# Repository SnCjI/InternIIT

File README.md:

# Microscope Illumination Drivers — IIT Kharagpur Summer Internship 2026

Hi! This is where I keep everything I built during the **IEEE EMBS Summer Internship 2026** at IIT Kharagpur. The internship was virtual, organized by the IEEE EMBS Student Branch Chapter, the IEEE Student Branch and the IEEE Kharagpur Section.

My task was to design the electronics that illuminate the sample in a scanning microscope. I worked on it in two phases:

- [**Phase 1 — Multispectral LED driver**](phase1-led-driver/): a board that powers five high-power LEDs (UV, blue, green, red and near-infrared). An ESP32 dims each color with PWM, and a MEAN WELL LDD-H module keeps the current steady. This phase is finished: it's designed, simulated and ready to send to a PCB manufacturer.
- [**Phase 2 — DPSS laser driver**](phase2-dpss-laser-driver/): a board that drives four DPSS lasers, starting with a Thorlabs DJ532-40 (532 nm, green). A Raspberry Pi Pico 2 sets each laser's current and decides exactly when each one turns on, in step with the camera and the motorized stage. The design is complete in simulation, and a few details are waiting on my supervisor.

One thing to know up front: **I did all of this in simulation.** I didn't buy parts or build a board. The results come from circuit simulators (Proteus and ngspice), firmware simulators (Velxio, Wokwi, a PIO emulator and a board model I wrote in Python) and KiCad's design checks. Both boards are ready to be manufactured, but neither has been tested on a real bench yet.

<p align="center">
  
  <br><em>The Phase 2 setup: the PC runs the camera and the stage, and my board handles the lasers.</em>
</p>

---

## The idea behind both boards

When a microscope takes pictures at several wavelengths, the light source has two jobs. It has to switch colors quickly, and it has to give the same amount of light every single time. I approached both phases the same way.

First, I kept "how much current" separate from "when". A dedicated analog circuit regulates the current through the LED or laser, so the microcontroller never carries that current. It only decides when the light is on and what the target current should be.

Second, I let the hardware handle the timing. In Phase 1, the ESP32's LEDC peripheral generates the PWM by itself. In Phase 2, the Pico 2's PIO state machines switch the lasers and record the camera and stage signals with nanosecond resolution, without the CPU getting involved.

Third, I tried to catch problems before building anything. I simulated each block on its own and then together, and I kept fixing the PCBs until KiCad's electrical and design-rule checks came back clean.

---

## What I've done so far

### Phase 1: the LED driver (October 2026)

I started by writing the requirements for a five-channel driver and drew the schematic in KiCad, then laid out a two-layer 118 × 43 mm board. Both passed KiCad's checks with zero errors.

Before routing, I went through every connection against the datasheets. That review caught two mistakes that would have made the board useless: the transistor's pins were in the wrong order, and the LEDs were wired backwards. I also wrote the ESP32 firmware, which takes simple text commands over USB, and tested it in a simulator.

In Proteus and ngspice I checked three things: that the current stays steady, that the PWM switches cleanly, and that the LED's average current follows the duty cycle in a straight line. To finish the phase, I prepared everything a manufacturer needs (Gerbers, drill files, parts list and placement file) and wrote the report in IEEE format.

The step-by-step details are in [`phase1-led-driver/`](phase1-led-driver/).

### Phase 2: the laser driver (November 2026)

The requirements went through three revisions with my supervisor. To know what I was driving, I built an ngspice model of the DJ532-40 laser and fitted it to its datasheet.

Then I designed the current channel. It gives 160 mA per volt, has a hardware limit at 400 mA, and switches in 8.3 µs without overshooting. The full schematic uses 183 real parts across several sheets, and it goes on a four-layer 170 × 120 mm board that passes all of KiCad's checks.

Safety got its own circuit. The key switch, the interlock, a temperature signal and a watchdog all have to agree before the lasers can turn on. When I simulated it, I found that in the worst case it cut the laser off too slowly: 1.45 ms, against a 1 ms requirement. I fixed it in a second revision (Rev B), which brought it down to 0.18 ms.

The firmware is in MicroPython and uses the Pico's PIO for the timing. There's also a Python client for the PC. It passes 15 out of 15 unit tests, and I also ran it on a virtual Pico.

Finally, I simulated the whole system, including how the camera reads its sensor one line at a time. That simulation showed which camera setting has to be used; with the wrong one, most of the image comes out dark. I closed the phase with the Rev B fabrication files and an IEEE-format report.

The step-by-step details are in [`phase2-dpss-laser-driver/`](phase2-dpss-laser-driver/).

---

## What comes next

These are the next steps, roughly in the order I'd tackle them:

1. **Confirm the open details with my supervisor**: the voltage and direction of the stage's BNC signal, what form the temperature-OK signal takes, the camera settings (Status Expos and trigger mode), and the specs of the other three lasers.
2. **Use a bigger −3.3 V converter in Phase 2.** With all four lasers at 400 mA, the current converter runs at 77 % of its rating. A 5 A part such as the LM2678-ADJ would bring it under my 50 % target.
3. **Re-run the Phase 2 current-channel simulation** with the manufacturers' own models of the OPA4197 and NDT3055L.
4. **Make a Phase 1 board v1.1.** It needs pull-up resistors on the PWM inputs so the LEDs stay off while the ESP32 boots, and screw terminals in place of the LED footprints for the COB LEDs.
5. **Build the boards and measure them**: the LDD-H dimming, how fast the laser really responds, the safety-chain timing and the PC trigger delay. The Phase 2 board time-stamps most of this on its own.
6. **Calibrate each laser** and give each one its own current limit.
7. **Improve the firmware.** One rule is too cautious, and relaxing it would save about 57 ms at every stage position. I'd also add a check that confirms the camera setting before each scan starts.

---

## Repository map

```
.
├── README.md                     ← you are here
├── docs/images/                  figures used in the READMEs
├── phase1-led-driver/
│   ├── README.md                 step-by-step explanation of Phase 1
│   ├── report/                   IEEE-format report (PDF)
│   ├── kicad/                    KiCad 10 project (schematic + PCB)
│   ├── fabrication/              Gerbers, drill, BOM, positions, schematic PDF, ready-to-order ZIP
│   ├── firmware/                 ESP32 Arduino sketch
│   └── simulation/               Proteus projects, ngspice netlist, CSV results, plots
└── phase2-dpss-laser-driver/
    ├── README.md                 step-by-step explanation of Phase 2
    ├── docs/                     IEEE-format report + requirements & architecture (Rev 3)
    ├── kicad/                    KiCad 10 hierarchical project (5 sheets + PCB)
    ├── fabrication/              Gerbers (4 layers), drill, BOM, positions, PCB images, ZIP (Rev B)
    ├── firmware/                 MicroPython + PIO firmware, PC client, simulators and tests
    └── simulation/               ngspice and Python simulations, Steps 1, 2, 4 and 6
```

## Tools I used

KiCad 10 · Freerouting · Proteus 8 · ngspice · Python (NumPy, Matplotlib) · Arduino / ESP32 · MicroPython · Raspberry Pi Pico 2 PIO · Wokwi · Velxio

## About me

**Julia Isabel Sanchez Cruz**, a 4th-year Electronic Engineering student.
Summer Internship 2026 (virtual), IEEE EMBS SBC, IEEE SB and IEEE Kharagpur Section, IIT Kharagpur.

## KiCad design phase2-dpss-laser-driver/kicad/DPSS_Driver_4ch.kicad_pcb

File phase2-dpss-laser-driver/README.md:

# Phase 2 — Four-Channel DPSS Laser Driver with Camera and Stage Synchronization

**Raspberry Pi Pico 2 (MicroPython + PIO) · DAC8565 · OPA4197 / NDT3055L current sinks · hardware safety chain · KiCad 10 · ngspice / Python**

Phase 2 replaces the LEDs of Phase 1 with **DPSS lasers** (diode-pumped solid-state), starting with the **Thorlabs DJ532-40** (532 nm, 40 mW), and adds what a scanning microscope needs: every image must be taken **with exactly one laser on, at a known time, after the stage has stopped moving**.

The system has three players:

- **Host PC (the master):** holds the scan plan, moves the Holmarc XYZ-θ stage, controls the PCO.panda 4.2 bi camera and stores the images.
- **Driver board (this project):** a Pico 2 that sets the four laser currents and switches each laser on and off in sync with the stage and camera signals.
- **Hardware safety chain:** key switch, interlock, temperature-OK and a watchdog that cut the laser current **without depending on the firmware**.

As in Phase 1, everything was verified in simulation; no hardware was built.

Report (IEEE format): [`docs/DPSS_Laser_Driver_Phase2_Report_IEEE.pdf`](docs/DPSS_Laser_Driver_Phase2_Report_IEEE.pdf)
Requirements and architecture, Rev 3: [`docs/DPSS_Laser_Driver_Phase2_Requirements_Architecture_Rev3.pdf`](docs/DPSS_Laser_Driver_Phase2_Requirements_Architecture_Rev3.pdf)

---

## How one stage position works

For every position of the snake-by-row scan, the board runs this sequence once per laser. The Pico's PIO state machines execute it in hardware, so the CPU doesn't have to:

```
stage "in position" edge → wait SETTLE → laser k ON → wait LEAD (laser output stabilizes)
→ camera exposure → camera's Status Expos falls → laser k OFF (13 ns later) → wait GAP → next laser
```

Each image therefore gets light from only one laser. Two more state machines time-stamp every stage and camera edge with nanosecond resolution and send the time stamps to the PC.

---

## Step by step: what was done

### Step 0 — Requirements and architecture (3 revisions)

The supervisor set the main decisions: four lasers switched only through their drive current, the PC as master, Python as the language, microsecond-level trigger timing, and the camera treated as something that must never be put at risk. From these I wrote 23 requirements, grouped as functional (F), electrical (E), safety (S), interface (I) and thermal (T), each with a test. The document went through **three revisions**. Revision 3 corrected a camera setting that the simulation in Step 6 showed was wrong.

### Step 1 — A model of the laser

The DJ532-40 was modeled in **ngspice**: a pump diode fitted to the datasheet's voltage curve, plus a green output that grows with the square of the current above threshold (the laser uses frequency doubling), P = K(I − I<sub>th</sub>)², with K = 1.027 W/A² and I<sub>th</sub> = 162 mA.

The datasheet does not give the optical response time τ, so I swept it from 10 µs to 1 ms. With a **5 ms lead time** before each exposure, the light deficit is below 0.07 % even in the worst case.

### Step 2 — One current channel

Each channel is a **linear current sink**: no switching ripple and a predictable step response. That matters because the DJ532-40 has only 70 mA between its typical (330 mA) and maximum (400 mA) current. The laser's case is its anode, so the anode stays at ground and the current is pulled from the cathode into a −3.3 V rail.

The DAC voltage passes an analog switch only when ENABLE **and** LASER_ON are high. It is then clamped to 2.5 V, level-shifted and fed to the control amplifier, which drives an NDT3055L MOSFET over a 1 Ω sense resistor. The result is **I = 160 mA/V × V<sub>DAC</sub>**, with a hardware ceiling of **400 mA** at the 2.5 V clamp.

| Test | Result |
|---|---|
| DC transfer | 160.00 mA/V, offset 0.08 mA |
| Hardware clamp (DAC up to 3.3 V) | 400.1 mA |
| Switching | 10–90 % in 8.3 µs, **0 % overshoot** |
| Power-up with the DAC at 3.3 V | 0.000 mA |
| Reverse voltage kick | 0.47 V (laser limit 2 V) |
| Compliance at −5 % rail | 400 mA with V<sub>DS</sub> = 0.54 V |

### Step 3 — Full schematic with real parts

A hierarchical KiCad project: a top sheet, power, controller (Pico 2, DAC, camera, stage and temperature interfaces), safety, and one laser-channel sheet used four times. In total **183 parts and 144 nets**.

| Function | Part |
|---|---|
| Controller | Raspberry Pi Pico 2 (RP2350) |
| Set-point DAC | DAC8565, 16 bit, 4 channels, 2.5 V reference |
| Op-amps | OPA4197 (quad) |
| Current sink | NDT3055L (SOT-223) |
| Safety logic | 74LVC2G17 Schmitt buffer, 74LVC1G11 AND, 74LVC2G74 latch, TPS3823 watchdog |
| Laser short when disabled | G6K-2F-Y relay |
| Power | LM2596S-5.0, LM2596S-ADJ (inverting, −3.31 V), TPS60403 (−5 V) |

### Step 4 — Safety chain simulation (and the Rev B fix)

The key switch and interlock close a CHAIN line. CHAIN, TEMP_OK and the watchdog go into an AND gate that clears a latch. The latch output is **ENABLE**, which gates all four channels, releases the shorting relays and lights the emission LED. ENABLE comes back only when everything is OK **and** the firmware sends a reset edge.

I simulated the whole path, from the interlock contact to the laser light. **This found a real problem.** With the original 10 kΩ/100 nF filter, CHAIN falls slowly into a normal CMOS input. With typical thresholds the laser turned off in 0.82 ms, but with the worst-case input threshold it took **1.45 ms**, which fails the 1 ms requirement.

**Rev B** added a Schmitt buffer (74LVC2G17) and reduced the capacitor to 10 nF. Worst case is now **0.18 ms**.

| Case | Current below 1 % | Requirement S1 (≤ 1 ms) |
|---|---|---|
| Interlock, Rev A, typical | 0.82 ms | Pass |
| Interlock, Rev A, worst case | 1.45 ms | **Fail** |
| Interlock or key, Rev B | 0.18 ms | Pass |
| TEMP_OK lost, Rev B | 0.075 ms | Pass |
| Watchdog reset | 0.032 ms | Pass |

### Step 5 — Firmware (MicroPython + PIO)

The firmware is six MicroPython files, and only one of them (`hw_pico.py`) touches the hardware. That lets the same core run on the Pico and in the PC simulators. Three PIO programs handle the timing: `frame_seq` runs the frames, `edge_ts` time-stamps edges, and `pulse` drives the stage output.

Safety in firmware: at power-up everything is zero and disabled. Set points above the per-laser limit (default 330 mA) are rejected. Any fault switches the lasers off, zeroes the DAC and **stops feeding the watchdog**, so the hardware latch opens too.

With no hardware available, the firmware was validated four ways:

| Check | Result |
|---|---|
| PIO opcodes vs. an independent assembler | 36/36 identical |
| MicroPython syntax (mpy-cross) | 6/6 files compile |
| Unit tests against the requirements | **15/15 pass** |
| Interval error (100 random intervals, cycle-accurate) | ≤ 3.3 ns (requirement 1 µs) |
| Time-stamp error (120 edges) | ≤ 6.7 ns |
| End of exposure → laser off | 13.3 ns |
| Snake scan 4 × 5 positions × 4 lasers | 80/80 images correctly lit |
| Real firmware on a virtual Pico (Wokwi) | Boot, fault, hardware-timed frame: OK |

Two bugs were found and fixed this way: the stage and camera pins were not configured as inputs, and the main loop did not yield to the USB stack.

See [`firmware/README.md`](firmware/README.md) for the full command set and how to run the verification (`python run_all.py`).

### Step 6 — Camera and stage synchronization

The PC client ran complete snake scans against the simulated board, with a **rolling-shutter camera model** built from the pco.panda manual. The camera's 2048 lines start one after another, 12.17 µs apart, so the last line starts 24.9 ms after the first.

**Finding 1: the camera setting matters.** The board turns the laser off when the camera's Status Expos signal falls, so that signal has to cover the exposure of *every* line. Only the setting **"Status Expos = overall time of All lines"** lights every row. With "First Line", 1555 of the 2048 rows got less than half the light, and that is the kind of mistake no electrical check would ever catch. Revision 2 of the requirements had specified a different setting; Revision 3 fixes it.

**Finding 2: who triggers the camera.** I compared mode B (the board triggers the camera) with mode A (the PC triggers it by software), using three assumed PC latency profiles. Each case ran 400 images:

| Mode | Exposure start after laser stable | Unused light per image | 4 × 5 scan time |
|---|---|---|---|
| B (board) | 0.031 ms | 5.0 ms | 10.44 s |
| A1 (tuned PC loop) | 1.5 ms | 6.5 ms | 10.57 s |
| A2 (typical Python) | 3.4 ms | 8.4 ms | 10.71 s |
| A3 (15.6 ms Windows timer) | 9.9 ms | 14.9 ms | 11.23 s |

Every image came out correct in every mode: a late trigger costs time, not images. **Mode A is recommended** because it needs no electrical connection to the camera input, and it only costs 1–8 % of scan time. Mode B is still on the board for when repeatable microsecond timing is needed.

### Step 7 — PCB and fabrication package (Rev B)

- **Four layers, 170 × 120 mm.** Power at the top left, Pico 2 in the center, camera, stage and safety at the top right, and the four channels along the bottom, each next to its laser connector.
- **Layer stack:** In1 is a solid ground plane. In2 carries the −3.3 V laser rail under the channels and ground elsewhere. Each MOSFET drain has its own copper area for heat.
- **Routing:** done with Freerouting using net classes (1 mm for laser currents, 0.3 mm for power, 0.25 mm for signals).
- **Checks:** KiCad 10 **ERC 0 errors**; **DRC 0 errors, 0 unconnected, 0 parity differences**. The checks were repeated after Rev B.

### Thermal check and test report

The laser channels are well within margin (the MOSFET runs at 35 % of its rating). **The weak point is the −3.3 V inverting converter.** With all four lasers at 400 mA its switch reaches 2.3 A peak, which is 77 % of its 3 A rating. That's above the 50 % target, although at the default 330 mA limit it drops to 65 %.

The test report has 19 test cases: **17 pass**. TC-07 is the failure that led to Rev B (fixed and re-tested as TC-08), and TC-19 (thermal and stress margin) passes only partly because of the converter.

---

## Future objectives for Phase 2

**Waiting on the supervisor**
- [ ] Confirm the stage's BNC signal: voltage level, direction and real step time (300 ms was assumed)
- [ ] Confirm the electrical form of the temperature-OK signal
- [ ] Confirm the camera settings: Status Expos = "overall time of All lines", and trigger mode A
- [ ] Get the specifications of the other three DPSS lasers

**Design improvements**
- [ ] Upsize the −3.3 V converter to a 5 A part (for example LM2678-ADJ with a 5 A Schottky), or use one converter per two channels
- [ ] Repeat the Step 2 simulation with the vendor SPICE models of the OPA4197 and NDT3055L
- [ ] Relax the firmware GAP rule (GAP + LEAD ≥ 25 ms is conservative), saving about 57 ms per stage position
- [ ] Before every scan, have the PC compare the measured Status Expos width with the expected value (exposure + 24.9 ms) to catch a wrong camera setting

**Hardware**
- [ ] Fabricate and assemble the board
- [ ] Measure the real DPSS response time τ (a short τ allows a shorter LEAD), the safety-chain timing, and the PC trigger latency using the board's own time stamps
- [ ] Calibrate the current limit of each laser module

---

## Folder contents

| Path | What is inside |
|---|---|
| `docs/` | Phase 2 report (IEEE, 8 pages) and Requirements & Architecture Rev 3 (7 pages) |
| `kicad/` | KiCad 10 hierarchical project: `DPSS_Driver_4ch.kicad_sch` (top), `power`, `controller`, `safety`, `laser_channel` sheets, `.kicad_pcb`, `.kicad_pro` |
| `fabrication/gerbers/` | 4 copper, 2 mask, 2 paste, 2 silkscreen, outline, job file, PTH/NPTH drill + drill maps |
| `fabrication/assembly/` | Grouped BOM and pick-and-place file |
| `fabrication/docs/` | Schematic PDF, top/bottom PCB images, Gerber preview |
| `fabrication/DPSS_Driver_4ch_Fabrication_Package_RevB.zip` | Everything above in one file, ready to send to a PCB maker |
| `firmware/firmware/` | The six MicroPython files that go on the Pico 2 |
| `firmware/pc/` | PC client (pyserial) and a snake-scan example |
| `firmware/sim/` | PIO assembler check, PIO emulator runs, board model, unit tests, Step 6 camera models; results in `sim/results/` |
| `firmware/wokwi/` | Files to run the firmware on a virtual Pico in Wokwi |
| `simulation/Step1_DPSS_model/` | ngspice laser model and fit |
| `simulation/Step2_Current_channel/` | ngspice channel tests (DC, gate, power-up, reverse, compliance) |
| `simulation/Step4_Safety_chain/` | ngspice/XSPICE safety-chain cases A–E, results CSV |
| `simulation/Step6_Camera_modes/` | Rolling-shutter results, mode A vs B, Status Expos settings |

Each simulation folder has its own `README.txt` with the exact commands to re-run it.

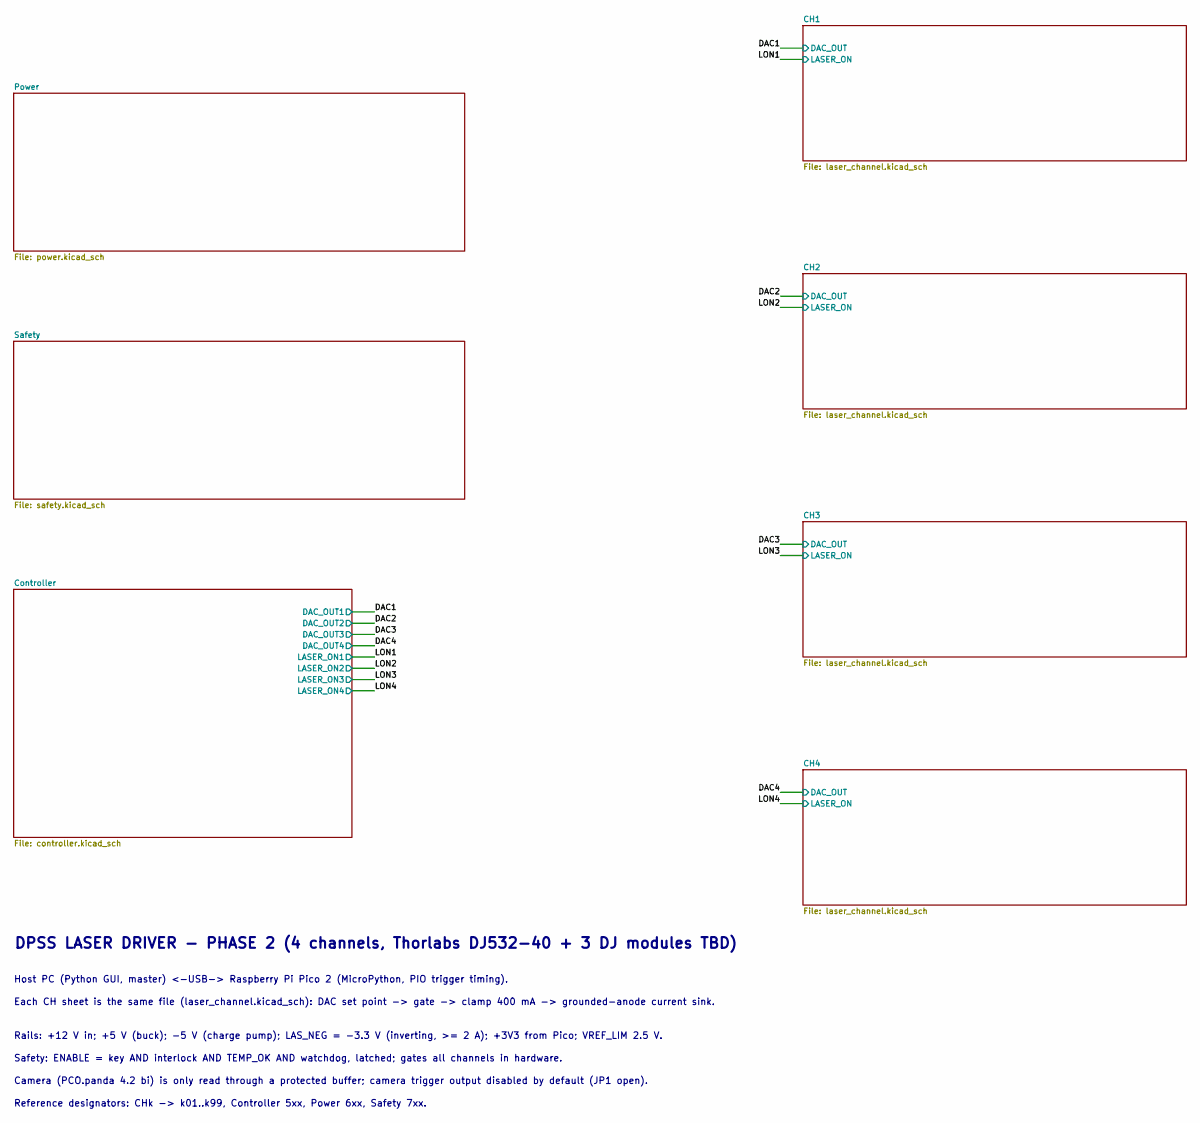
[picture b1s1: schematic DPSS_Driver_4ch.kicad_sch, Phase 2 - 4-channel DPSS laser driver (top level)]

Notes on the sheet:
Reference designators: CHk -> k01..k99, Controller 5xx, Power 6xx, Safety 7xx.
Camera (PCO.panda 4.2 bi) is only read through a protected buffer; camera trigger output disabled by default (JP1 open).
Host PC (Python GUI, master) <-USB-> Raspberry Pi Pico 2 (MicroPython, PIO trigger timing).
DPSS LASER DRIVER - PHASE 2 (4 channels, Thorlabs DJ532-40 + 3 DJ modules TBD)
Safety: ENABLE = key AND interlock AND TEMP_OK AND watchdog, latched; gates all channels in hardware.
Rails: +12 V in; +5 V (buck); -5 V (charge pump); LAS_NEG = -3.3 V (inverting, >= 2 A); +3V3 from Pico; VREF_LIM 2.5 V.
Each CH sheet is the same file (laser_channel.kicad_sch): DAC set point -> gate -> clamp 400 mA -> grounded-anode current sink.

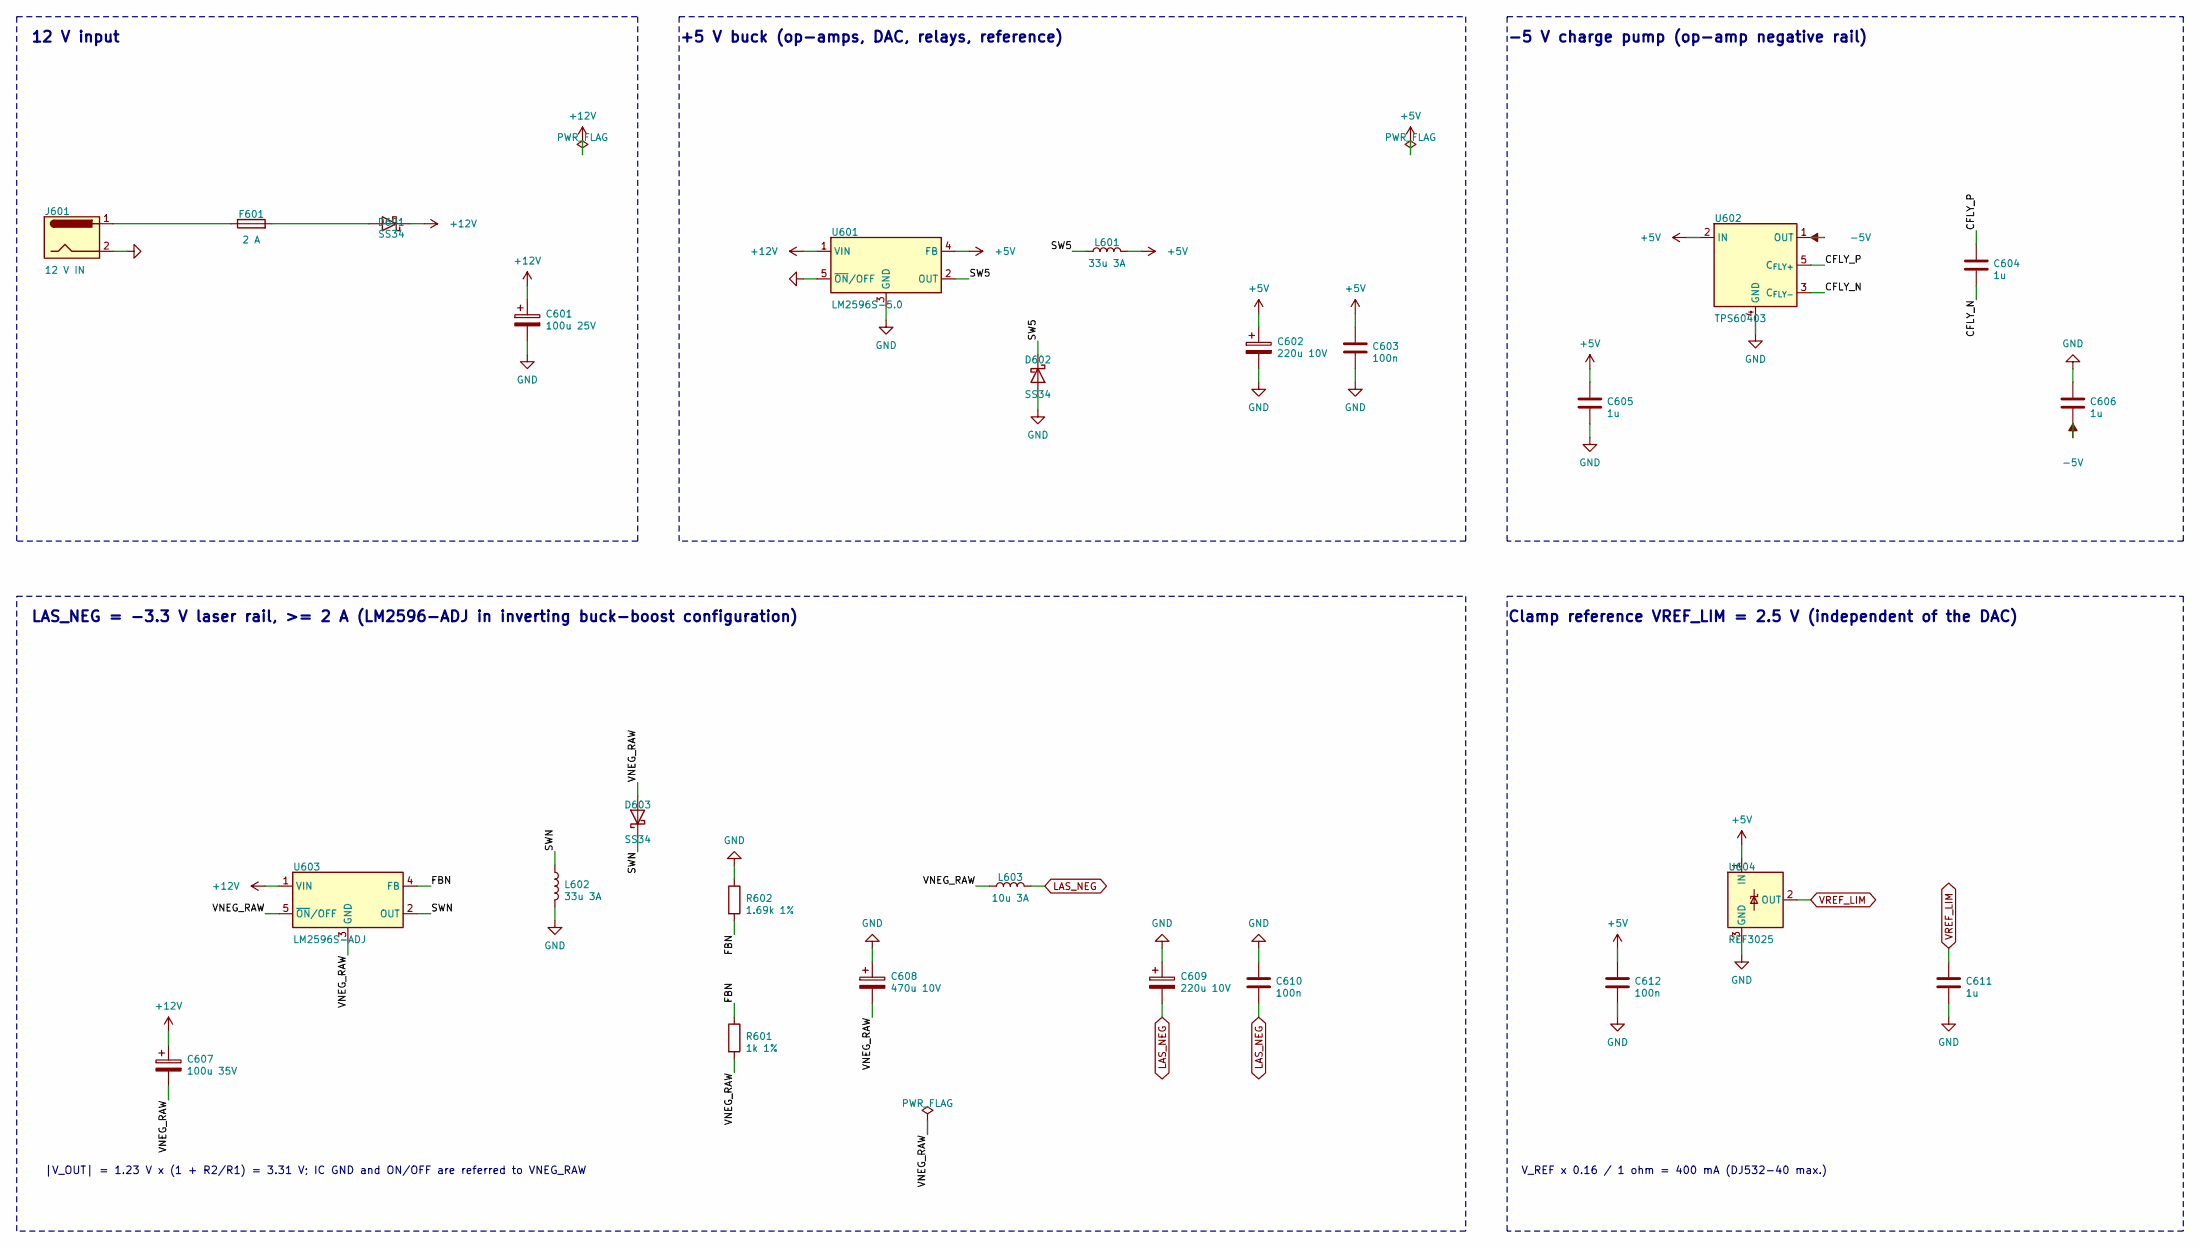
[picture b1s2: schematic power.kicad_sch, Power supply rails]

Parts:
C601: 100u 25V; CP_Elec_8x10
C602, C609: 220u 10V; CP_Elec_8x10
C603, C610, C612: 100n; C_0805_2012Metric
C604, C605, C606, C611: 1u; C_0805_2012Metric
C607: 100u 35V; CP_Elec_8x10
C608: 470u 10V; CP_Elec_10x10
D601, D602, D603: SS34; D_SMA
F601: 2 A; Fuse_1812_4532Metric
J601: 12 V IN; BarrelJack_Horizontal
L601, L602: 33u 3A; L_12x12mm_H8mm
L603: 10u 3A; L_6.3x6.3_H3
R601: 1k 1%; R_0805_2012Metric
R602: 1.69k 1%; R_0805_2012Metric
U601: LM2596S-5.0; TO-263-5_TabPin3
U602: TPS60403; SOT-23-5
U603: LM2596S-ADJ; TO-263-5_TabPin3
U604: REF3025; SOT-23

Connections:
+5V: C602.1, C603.1, C605.1, C612.1, L601.2, U601.4 (FB), U602.2 (IN), U604.1 (IN); also elsewhere on the board
+12V: C601.1, C607.1, D601.1 (K), U601.1 (VIN), U603.1 (VIN)
-5V: C606.2, U602.1 (OUT); also elsewhere on the board
/Power/CFLY_N: C604.2, U602.3 (C_{FLY-})
/Power/CFLY_P: C604.1, U602.5 (C_{FLY+})
/Power/FBN: R601.1, R602.2, U603.4 (FB)
/Power/SW5: D602.1 (K), L601.1, U601.2 (OUT)
/Power/SWN: D603.1 (K), L602.1, U603.2 (OUT)
/Power/VNEG_RAW: C607.2, C608.2, D603.2 (A), L603.1, R601.2, U603.3 (GND), U603.5 (~ON/OFF)
GND: C601.2, C602.2, C603.2, C605.2, C606.1, C608.1, C609.1, C610.1, C611.2, C612.2, D602.2 (A), J601.2, L602.2, R602.1, U601.3 (GND), U601.5 (~ON/OFF), U602.4 (GND), U604.3 (GND); also elsewhere on the board
LAS_NEG: C609.2, C610.2, L603.2; also elsewhere on the board
unnamed: D601.2 (A), F601.2
unnamed: F601.1, J601.1
VREF_LIM: C611.1, U604.2 (OUT); also elsewhere on the board

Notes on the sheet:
Clamp reference VREF_LIM = 2.5 V (independent of the DAC)
|V_OUT| = 1.23 V x (1 + R2/R1) = 3.31 V; IC GND and ON/OFF are referred to VNEG_RAW
+5 V buck (op-amps, DAC, relays, reference)
12 V input
-5 V charge pump (op-amp negative rail)
V_REF x 0.16 / 1 ohm = 400 mA (DJ532-40 max.)
LAS_NEG = -3.3 V laser rail, >= 2 A (LM2596-ADJ in inverting buck-boost configuration)

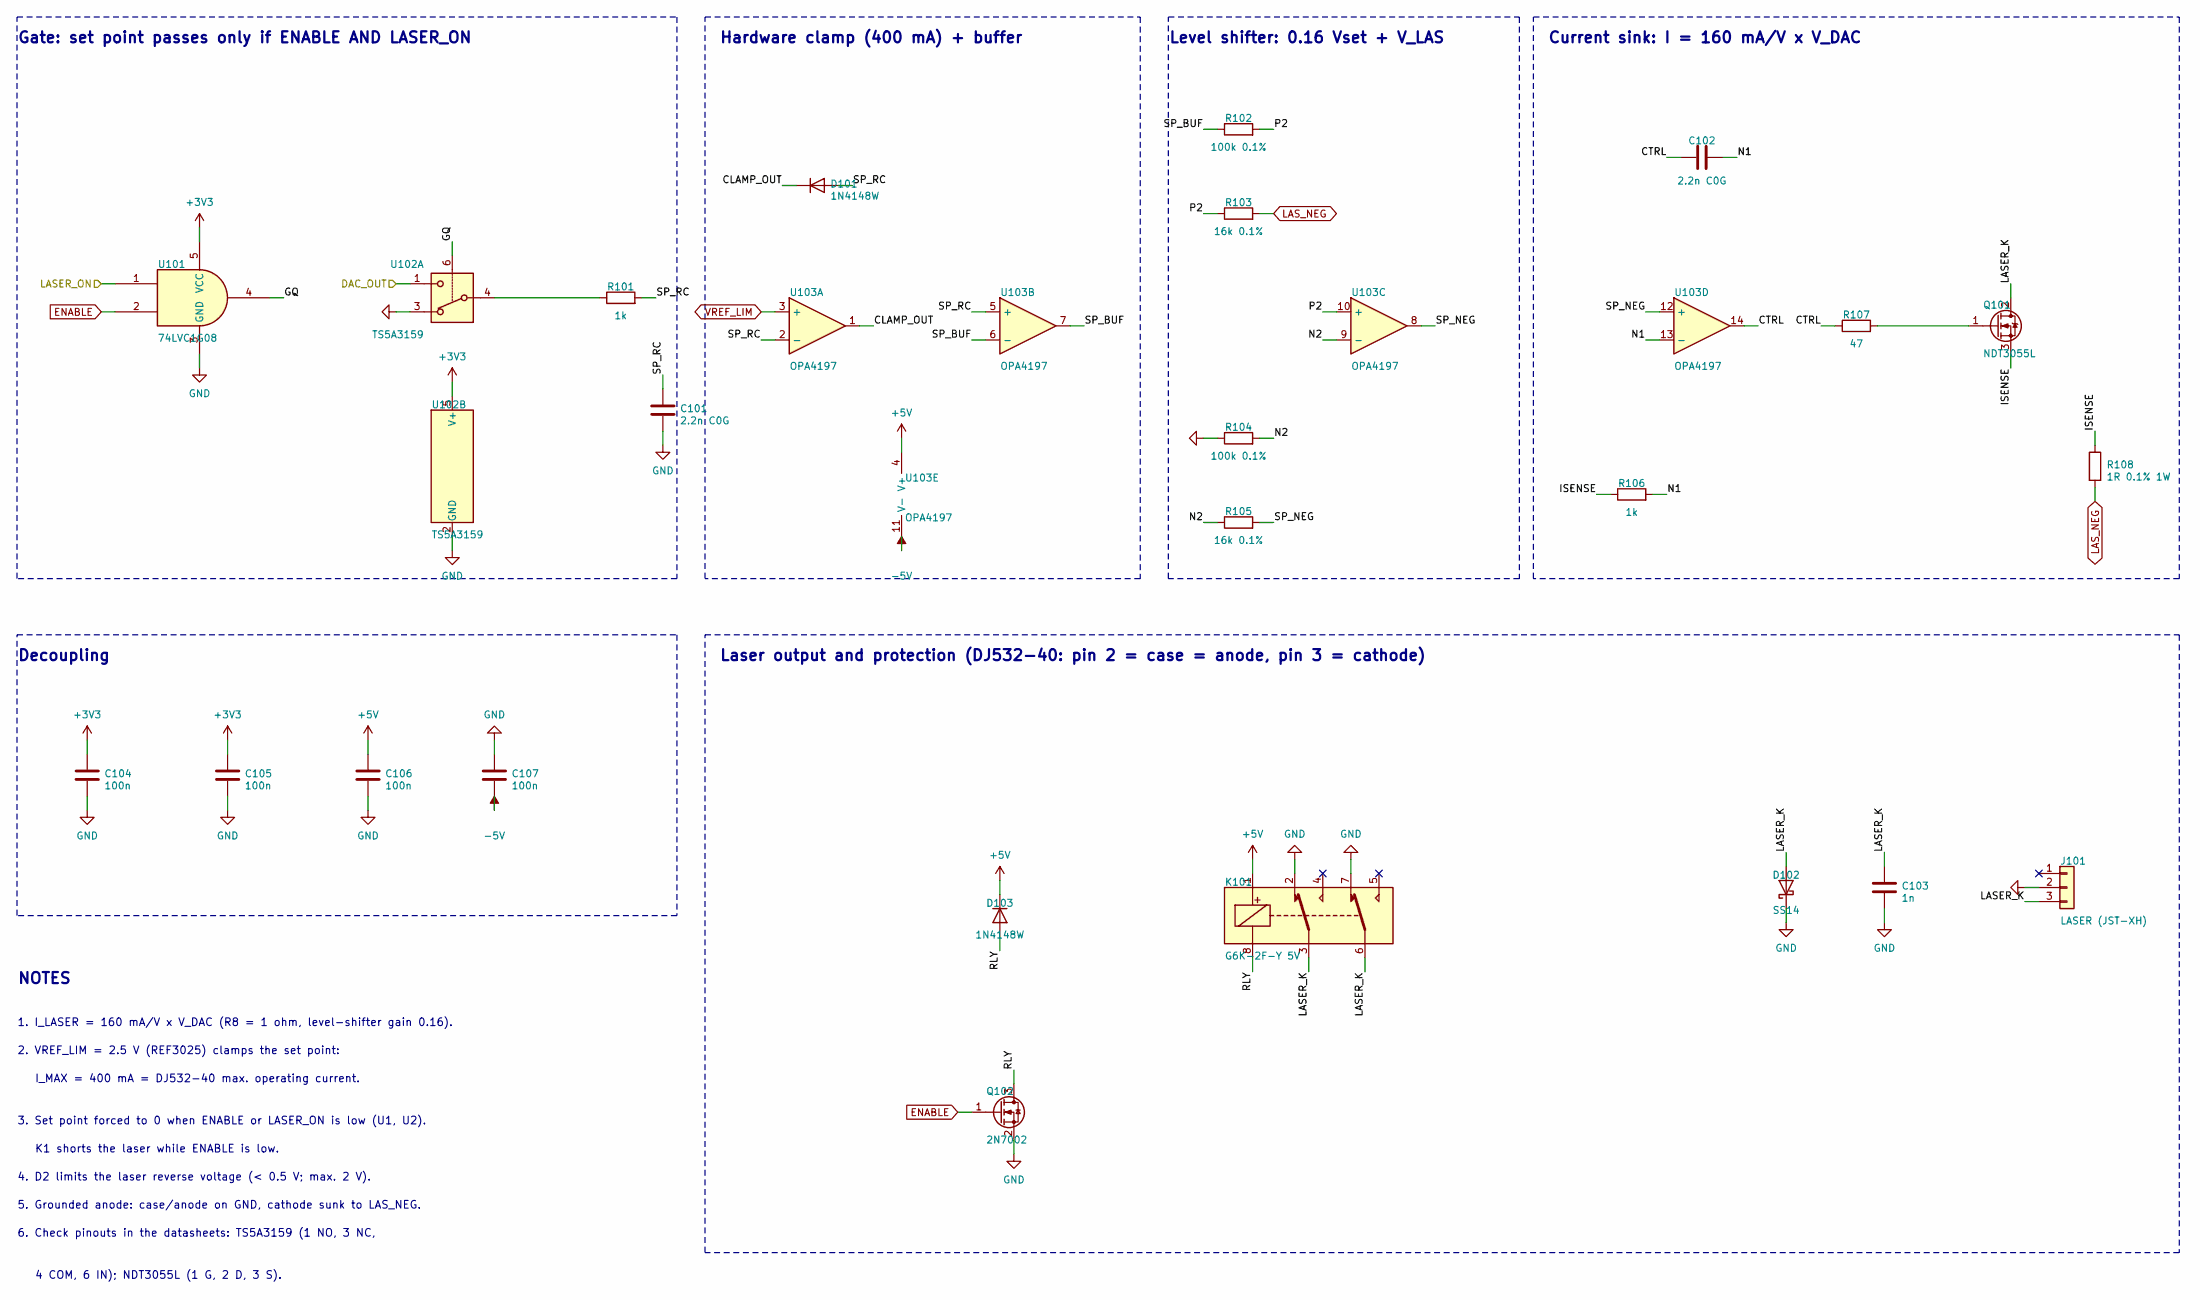
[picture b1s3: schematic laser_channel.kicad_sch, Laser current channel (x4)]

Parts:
C101, C102: 2.2n C0G; C_0805_2012Metric
C103: 1n; C_0805_2012Metric
C104, C105, C106, C107: 100n; C_0805_2012Metric
D101, D103: 1N4148W; D_SOD-123
D102: SS14; D_SMA
J101: LASER (JST-XH); JST_XH_B3B-XH-A_1x03_P2.50mm_Vertical
K101: G6K-2F-Y 5V; Relay_DPDT_Omron_G6K-2F-Y
Q101: NDT3055L; SOT-223-3_TabPin2
Q102: 2N7002; SOT-23
R101, R106: 1k; R_0805_2012Metric
R102, R104: 100k 0.1%; R_0805_2012Metric; Tolerance 0.1%
R103, R105: 16k 0.1%; R_0805_2012Metric; Tolerance 0.1%
R107: 47; R_0805_2012Metric
R108: 1R 0.1% 1W; R_2512_6332Metric; Tolerance 0.1%
U101: 74LVC1G08; SOT-23-5
U102: TS5A3159; SOT-23-6
U103: OPA4197; SOIC-14_3.9x8.7mm_P1.27mm

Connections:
+3V3: C104.1, C105.1, U101.5 (VCC), U102.5 (V+); also elsewhere on the board
+5V: C106.1, D103.1 (K), K101.1, U103.4 (V+); also elsewhere on the board
-5V: C107.2, U103.11 (V-); also elsewhere on the board
/CH1/CLAMP_OUT: D101.1 (K), U103.1
/CH1/CTRL: C102.1, R107.1, U103.14
/CH1/GQ: U101.4, U102.6
/CH1/ISENSE: Q101.3 (S), R106.1, R108.1
/CH1/LASER_K: C103.1, D102.2 (A), J101.3, K101.3, K101.6, Q101.2 (D)
/CH1/N1: C102.2, R106.2, U103.13 (-)
/CH1/N2: R104.2, R105.1, U103.9 (-)
/CH1/P2: R102.2, R103.1, U103.10 (+)
/CH1/RLY: D103.2 (A), K101.8, Q102.3 (D)
/CH1/SP_BUF: R102.1, U103.6 (-), U103.7
/CH1/SP_NEG: R105.2, U103.8, U103.12 (+)
/CH1/SP_RC: C101.1, D101.2 (A), R101.2, U103.2 (-), U103.5 (+)
/DAC1: U102.1; also elsewhere on the board
/LON1: U101.1; also elsewhere on the board
ENABLE: Q102.1 (G), U101.2; also elsewhere on the board
GND: C101.2, C103.2, C104.2, C105.2, C106.2, C107.1, D102.1 (K), J101.2, K101.2, K101.7, Q102.2 (S), R104.1, U101.3 (GND), U102.2 (GND), U102.3; also elsewhere on the board
LAS_NEG: R103.2, R108.2; also elsewhere on the board
unnamed: Q101.1 (G), R107.2
unnamed: R101.1, U102.4
VREF_LIM: U103.3 (+); also elsewhere on the board

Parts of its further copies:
C201, C202, C301, C302, C401, C402: 2.2n C0G; C_0805_2012Metric
C203, C303, C403: 1n; C_0805_2012Metric
C204, C205, C206, C207, C304, C305, C306, C307, C404, C405, C406, C407: 100n; C_0805_2012Metric
D201, D203, D301, D303, D401, D403: 1N4148W; D_SOD-123
D202, D302, D402: SS14; D_SMA
J201, J301, J401: LASER (JST-XH); JST_XH_B3B-XH-A_1x03_P2.50mm_Vertical
K201, K301, K401: G6K-2F-Y 5V; Relay_DPDT_Omron_G6K-2F-Y
Q201, Q301, Q401: NDT3055L; SOT-223-3_TabPin2
Q202, Q302, Q402: 2N7002; SOT-23
R201, R206, R301, R306, R401, R406: 1k; R_0805_2012Metric
R202, R204, R302, R304, R402, R404: 100k 0.1%; R_0805_2012Metric; Tolerance 0.1%
R203, R205, R303, R305, R403, R405: 16k 0.1%; R_0805_2012Metric; Tolerance 0.1%
R207, R307, R407: 47; R_0805_2012Metric
R208, R308, R408: 1R 0.1% 1W; R_2512_6332Metric; Tolerance 0.1%
U201, U301, U401: 74LVC1G08; SOT-23-5
U202, U302, U402: TS5A3159; SOT-23-6
U203, U303, U403: OPA4197; SOIC-14_3.9x8.7mm_P1.27mm

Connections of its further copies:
+3V3: C204.1, C205.1, C304.1, C305.1, C404.1, C405.1, U201.5 (VCC), U202.5 (V+), U301.5 (VCC), U302.5 (V+), U401.5 (VCC), U402.5 (V+); also elsewhere on the board
+5V: C206.1, C306.1, C406.1, D203.1 (K), D303.1 (K), D403.1 (K), K201.1, K301.1, K401.1, U203.4 (V+), U303.4 (V+), U403.4 (V+); also elsewhere on the board
-5V: C207.2, C307.2, C407.2, U203.11 (V-), U303.11 (V-), U403.11 (V-); also elsewhere on the board
/CH2/CLAMP_OUT: D201.1 (K), U203.1
/CH2/CTRL: C202.1, R207.1, U203.14
/CH2/GQ: U201.4, U202.6
/CH2/ISENSE: Q201.3 (S), R206.1, R208.1
/CH2/LASER_K: C203.1, D202.2 (A), J201.3, K201.3, K201.6, Q201.2 (D)
/CH2/N1: C202.2, R206.2, U203.13 (-)
/CH2/N2: R204.2, R205.1, U203.9 (-)
/CH2/P2: R202.2, R203.1, U203.10 (+)
/CH2/RLY: D203.2 (A), K201.8, Q202.3 (D)
/CH2/SP_BUF: R202.1, U203.6 (-), U203.7
/CH2/SP_NEG: R205.2, U203.8, U203.12 (+)
/CH2/SP_RC: C201.1, D201.2 (A), R201.2, U203.2 (-), U203.5 (+)
/CH3/CLAMP_OUT: D301.1 (K), U303.1
/CH3/CTRL: C302.1, R307.1, U303.14
/CH3/GQ: U301.4, U302.6
/CH3/ISENSE: Q301.3 (S), R306.1, R308.1
/CH3/LASER_K: C303.1, D302.2 (A), J301.3, K301.3, K301.6, Q301.2 (D)
/CH3/N1: C302.2, R306.2, U303.13 (-)
/CH3/N2: R304.2, R305.1, U303.9 (-)
/CH3/P2: R302.2, R303.1, U303.10 (+)
/CH3/RLY: D303.2 (A), K301.8, Q302.3 (D)
/CH3/SP_BUF: R302.1, U303.6 (-), U303.7
/CH3/SP_NEG: R305.2, U303.8, U303.12 (+)
/CH3/SP_RC: C301.1, D301.2 (A), R301.2, U303.2 (-), U303.5 (+)
/CH4/CLAMP_OUT: D401.1 (K), U403.1
/CH4/CTRL: C402.1, R407.1, U403.14
/CH4/GQ: U401.4, U402.6
/CH4/ISENSE: Q401.3 (S), R406.1, R408.1
/CH4/LASER_K: C403.1, D402.2 (A), J401.3, K401.3, K401.6, Q401.2 (D)
/CH4/N1: C402.2, R406.2, U403.13 (-)
/CH4/N2: R404.2, R405.1, U403.9 (-)
/CH4/P2: R402.2, R403.1, U403.10 (+)
/CH4/RLY: D403.2 (A), K401.8, Q402.3 (D)
/CH4/SP_BUF: R402.1, U403.6 (-), U403.7
/CH4/SP_NEG: R405.2, U403.8, U403.12 (+)
/CH4/SP_RC: C401.1, D401.2 (A), R401.2, U403.2 (-), U403.5 (+)
/DAC2: U202.1; also elsewhere on the board
/DAC3: U302.1; also elsewhere on the board
/DAC4: U402.1; also elsewhere on the board
/LON2: U201.1; also elsewhere on the board
/LON3: U301.1; also elsewhere on the board
/LON4: U401.1; also elsewhere on the board
ENABLE: Q202.1 (G), Q302.1 (G), Q402.1 (G), U201.2, U301.2, U401.2; also elsewhere on the board
GND: C201.2, C203.2, C204.2, C205.2, C206.2, C207.1, C301.2, C303.2, C304.2, C305.2, C306.2, C307.1, C401.2, C403.2, C404.2, C405.2, C406.2, C407.1, D202.1 (K), D302.1 (K), D402.1 (K), J201.2, J301.2, J401.2, K201.2, K201.7, K301.2, K301.7, K401.2, K401.7, Q202.2 (S), Q302.2 (S), Q402.2 (S), R204.1, R304.1, R404.1, U201.3 (GND), U202.2 (GND), U202.3, U301.3 (GND), U302.2 (GND), U302.3, U401.3 (GND), U402.2 (GND), U402.3; also elsewhere on the board
LAS_NEG: R203.2, R208.2, R303.2, R308.2, R403.2, R408.2; also elsewhere on the board
unnamed: Q201.1 (G), R207.2
unnamed: Q301.1 (G), R307.2
unnamed: Q401.1 (G), R407.2
unnamed: R201.1, U202.4
unnamed: R301.1, U302.4
unnamed: R401.1, U402.4
VREF_LIM: U203.3 (+), U303.3 (+), U403.3 (+); also elsewhere on the board

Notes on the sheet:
Level shifter: 0.16 Vset + V_LAS
6. Check pinouts in the datasheets: TS5A3159 (1 NO, 3 NC,
NOTES
4 COM, 6 IN); NDT3055L (1 G, 2 D, 3 S).
Current sink: I = 160 mA/V x V_DAC
K1 shorts the laser while ENABLE is low.
Hardware clamp (400 mA) + buffer
2. VREF_LIM = 2.5 V (REF3025) clamps the set point:
3. Set point forced to 0 when ENABLE or LASER_ON is low (U1, U2).
4. D2 limits the laser reverse voltage (< 0.5 V; max. 2 V).
Decoupling
I_MAX = 400 mA = DJ532-40 max. operating current.
1. I_LASER = 160 mA/V x V_DAC (R8 = 1 ohm, level-shifter gain 0.16).
5. Grounded anode: case/anode on GND, cathode sunk to LAS_NEG.
Gate: set point passes only if ENABLE AND LASER_ON
Laser output and protection (DJ532-40: pin 2 = case = anode, pin 3 = cathode)

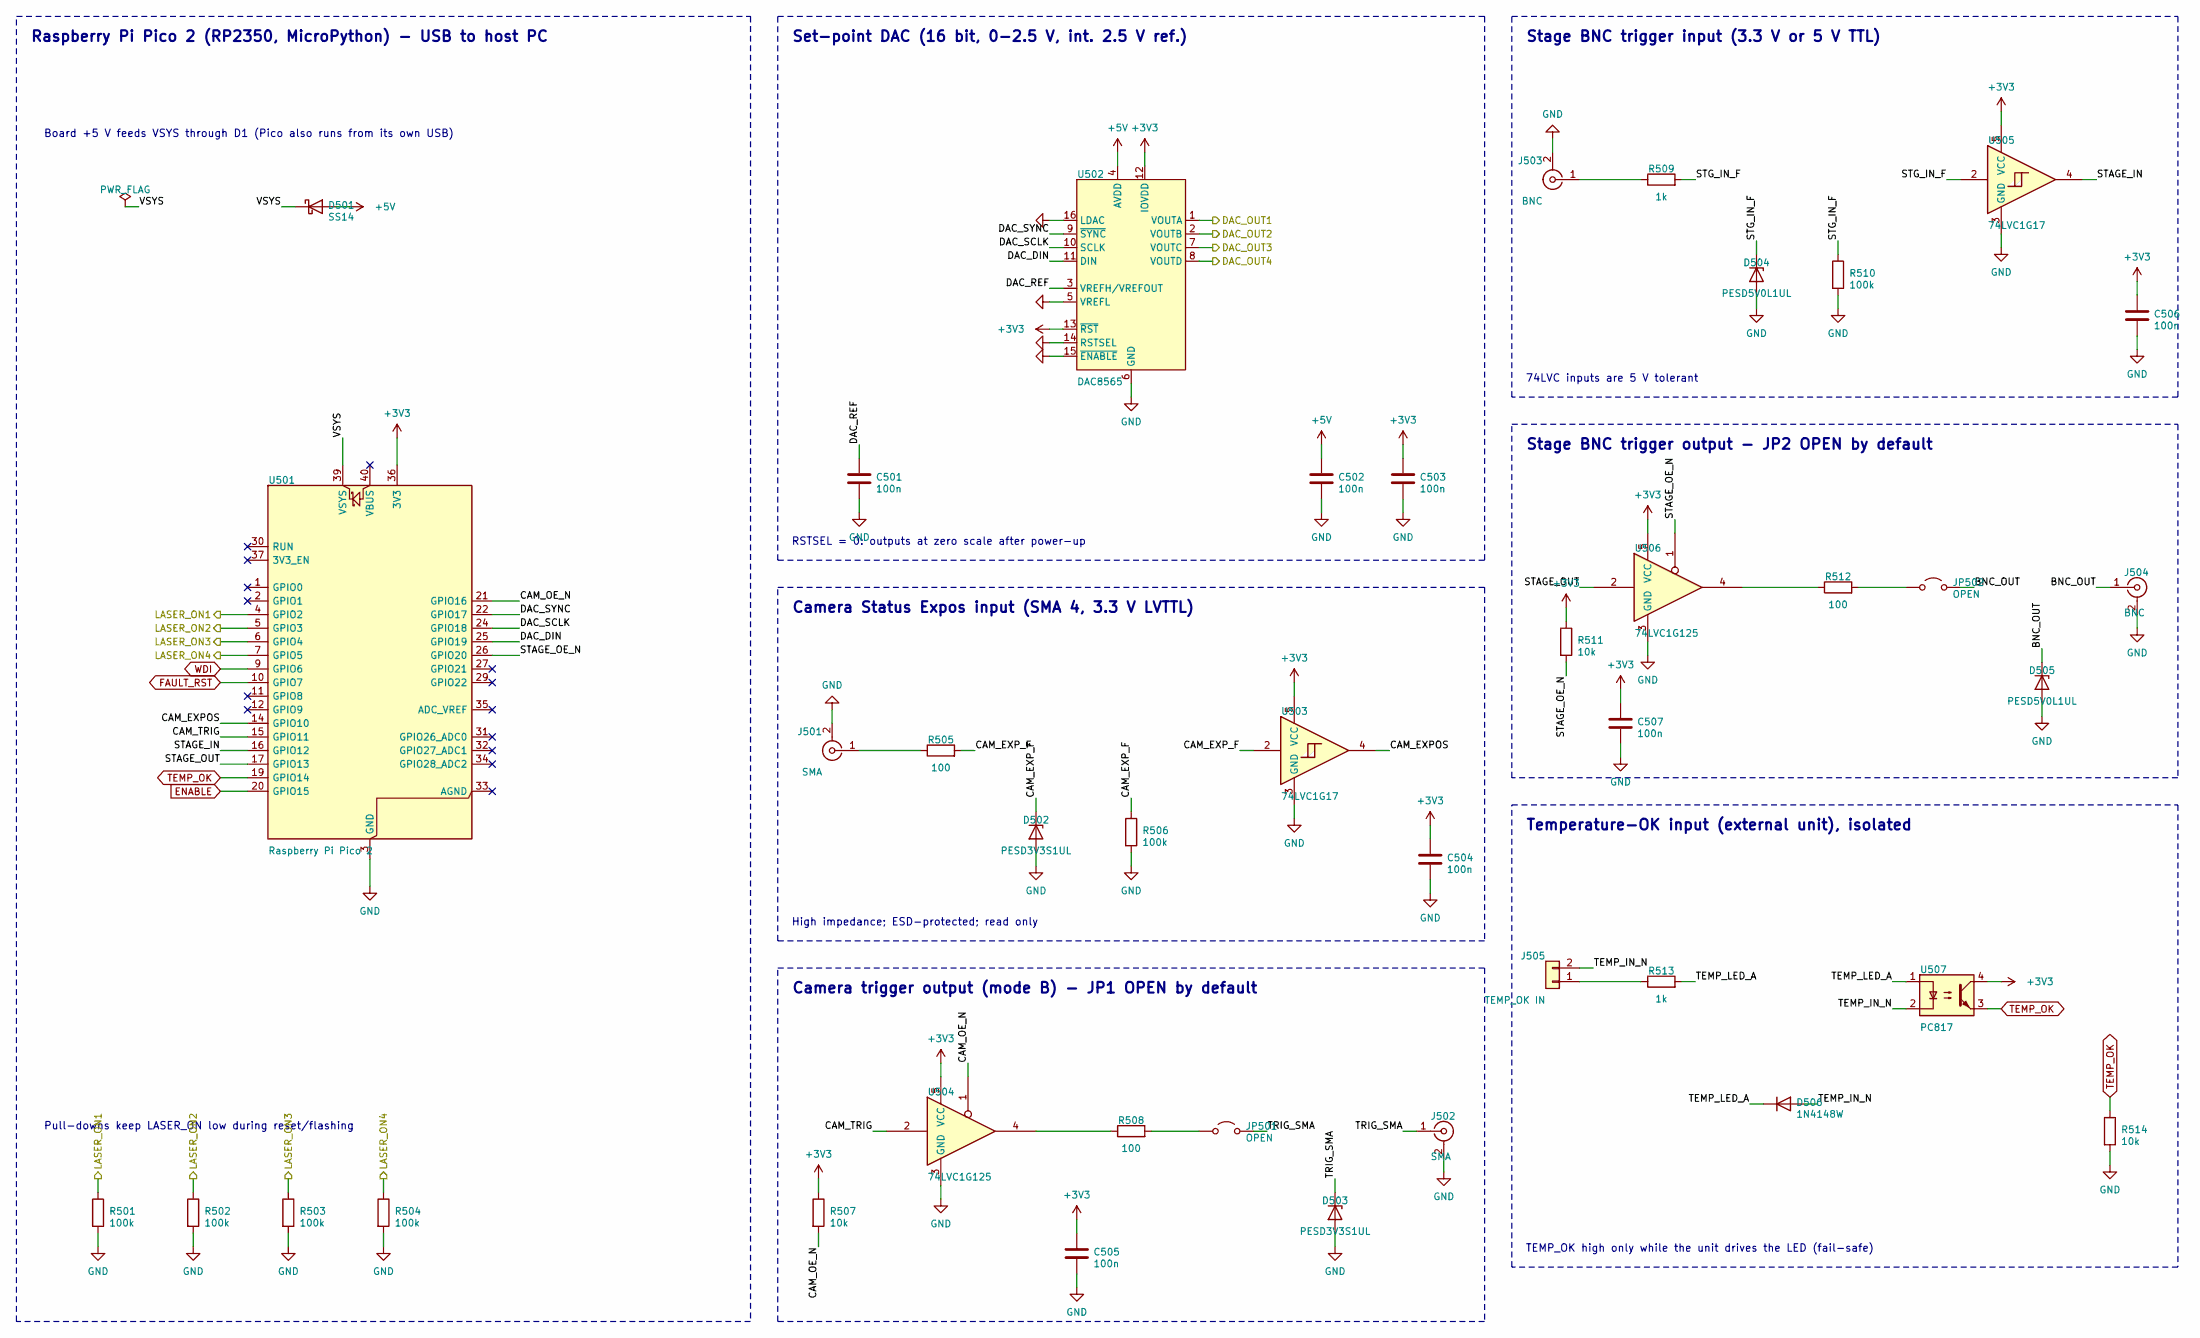
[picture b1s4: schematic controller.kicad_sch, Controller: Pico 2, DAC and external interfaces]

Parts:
C501, C502, C503, C504, C505, C506, C507: 100n; C_0805_2012Metric
D501: SS14; D_SMA
D502, D503: PESD3V3S1UL; D_SOD-882
D504, D505: PESD5V0L1UL; D_SOD-882
D506: 1N4148W; D_SOD-123
J501, J502: SMA; SMA_Amphenol_132134_Vertical
J503, J504: BNC; BNC_Amphenol_B6252HB-NPP3G-50_Horizontal
J505: TEMP_OK IN; JST_XH_B2B-XH-A_1x02_P2.50mm_Vertical
JP501, JP502: OPEN; PinHeader_1x02_P2.54mm_Vertical
R501, R502, R503, R504, R506, R510: 100k; R_0805_2012Metric
R505, R508, R512: 100; R_0805_2012Metric
R507, R511, R514: 10k; R_0805_2012Metric
R509, R513: 1k; R_0805_2012Metric
U501: Raspberry Pi Pico 2; RaspberryPi_Pico_Common_Unspecified
U502: DAC8565; TSSOP-16_4.4x5mm_P0.65mm
U503, U505: 74LVC1G17; SOT-23-5
U504, U506: 74LVC1G125; SOT-23-5
U507: PC817; DIP-4_W7.62mm

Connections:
+3V3: C503.1, C504.1, C505.1, C506.1, C507.1, R507.1, R511.1, U501.36 (3V3), U502.12 (IOVDD), U502.13 (~RST), U503.5 (VCC), U504.5 (VCC), U505.5 (VCC), U506.5 (VCC), U507.4; also elsewhere on the board
+5V: C502.1, D501.2 (A), U502.4 (AVDD); also elsewhere on the board
/Controller/BNC_OUT: D505.1 (K), J504.1 (In), JP502.2 (B)
/Controller/CAM_EXPOS: U501.14 (GPIO10), U503.4
/Controller/CAM_EXP_F: D502.1 (K), R505.2, R506.1, U503.2
/Controller/CAM_OE_N: R507.2, U501.21 (GPIO16), U504.1
/Controller/CAM_TRIG: U501.15 (GPIO11), U504.2
/Controller/DAC_DIN: U501.25 (GPIO19), U502.11 (DIN)
/Controller/DAC_REF: C501.1, U502.3 (VREFH/VREFOUT)
/Controller/DAC_SCLK: U501.24 (GPIO18), U502.10 (SCLK)
/Controller/DAC_SYNC: U501.22 (GPIO17), U502.9 (~SYNC)
/Controller/STAGE_IN: U501.16 (GPIO12), U505.4
/Controller/STAGE_OE_N: R511.2, U501.26 (GPIO20), U506.1
/Controller/STAGE_OUT: U501.17 (GPIO13), U506.2
/Controller/STG_IN_F: D504.1 (K), R509.2, R510.1, U505.2
/Controller/TEMP_IN_N: D506.2 (A), J505.2, U507.2
/Controller/TEMP_LED_A: D506.1 (K), R513.2, U507.1
/Controller/TRIG_SMA: D503.1 (K), J502.1 (In), JP501.2 (B)
/Controller/VSYS: D501.1 (K), U501.39 (VSYS)
/DAC1: U502.1 (VOUTA); also elsewhere on the board
/DAC2: U502.2 (VOUTB); also elsewhere on the board
/DAC3: U502.7 (VOUTC); also elsewhere on the board
/DAC4: U502.8 (VOUTD); also elsewhere on the board
/LON1: R501.1, U501.4 (GPIO2); also elsewhere on the board
/LON2: R502.1, U501.5 (GPIO3); also elsewhere on the board
/LON3: R503.1, U501.6 (GPIO4); also elsewhere on the board
/LON4: R504.1, U501.7 (GPIO5); also elsewhere on the board
ENABLE: U501.20 (GPIO15); also elsewhere on the board
FAULT_RST: U501.10 (GPIO7); also elsewhere on the board
GND: C501.2, C502.2, C503.2, C504.2, C505.2, C506.2, C507.2, D502.2 (A), D503.2 (A), D504.2 (A), D505.2 (A), J501.2 (Ext), J502.2 (Ext), J503.2 (Ext), J504.2 (Ext), R501.2, R502.2, R503.2, R504.2, R506.2, R510.2, R514.2, U501.3 (GND), U501.8 (GND), U501.13 (GND), U501.18 (GND), U501.23 (GND), U501.28 (GND), U501.38 (GND), U502.5 (VREFL), U502.6 (GND), U502.14 (RSTSEL), U502.15 (~ENABLE), U502.16 (LDAC), U503.3 (GND), U504.3 (GND), U505.3 (GND), U506.3 (GND); also elsewhere on the board
unnamed: J501.1 (In), R505.1
unnamed: J503.1 (In), R509.1
unnamed: J505.1, R513.1
unnamed: JP501.1 (A), R508.2
unnamed: JP502.1 (A), R512.2
unnamed: R508.1, U504.4
unnamed: R512.1, U506.4
TEMP_OK: R514.1, U501.19 (GPIO14), U507.3; also elsewhere on the board
WDI: U501.9 (GPIO6); also elsewhere on the board

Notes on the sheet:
74LVC inputs are 5 V tolerant
Camera Status Expos input (SMA 4, 3.3 V LVTTL)
TEMP_OK high only while the unit drives the LED (fail-safe)
Raspberry Pi Pico 2 (RP2350, MicroPython) - USB to host PC
High impedance; ESD-protected; read only
Camera trigger output (mode B) - JP1 OPEN by default
Set-point DAC (16 bit, 0-2.5 V, int. 2.5 V ref.)
RSTSEL = 0: outputs at zero scale after power-up
Board +5 V feeds VSYS through D1 (Pico also runs from its own USB)
Stage BNC trigger output - JP2 OPEN by default
Pull-downs keep LASER_ON low during reset/flashing
Stage BNC trigger input (3.3 V or 5 V TTL)
Temperature-OK input (external unit), isolated
